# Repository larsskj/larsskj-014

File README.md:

A board hosting pogo pins
=========================

### larsskj-014

This project is a board hosting a couple of pogo pins intended to supply power to structures and other scale models.

The board has a diameter of 29 mm intended to be mounted in a 30 mm hole. The distance between the pogo pins is 10 mm.

For more information, visit the [project homepage](https://larsskj.org/projects/larsskj-014).

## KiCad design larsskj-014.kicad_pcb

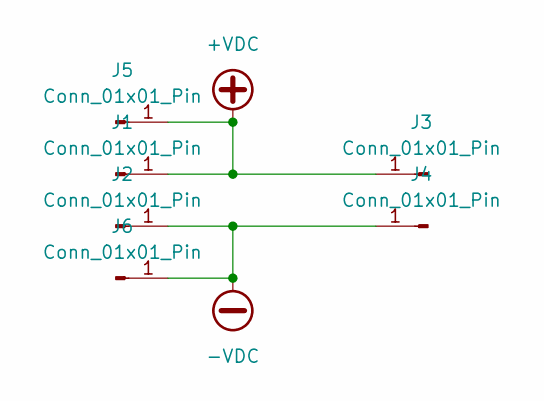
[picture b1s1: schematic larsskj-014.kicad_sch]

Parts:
J1, J2, J5, J6: Conn_01x01_Pin; MountingHole_2.2mm_M2_Pad_Via
J3, J4: Conn_01x01_Pin; Pogo_Pin_YZ227415084P-01; LCSC C5157269

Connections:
+VDC: J1.1, J3.1, J5.1
-VDC: J2.1, J4.1, J6.1

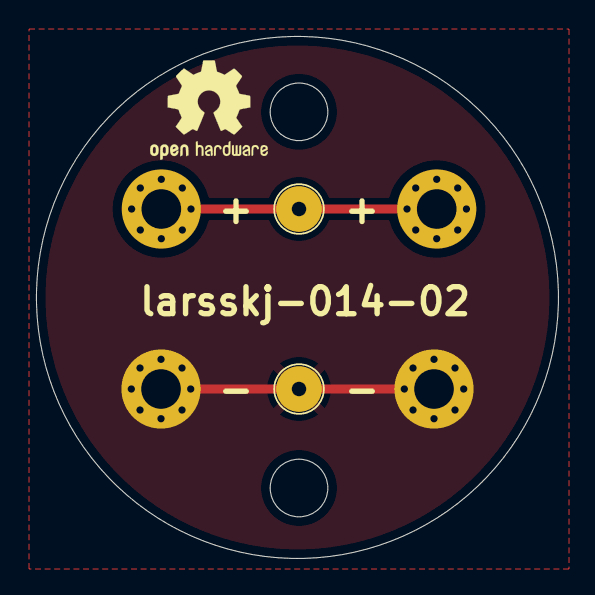
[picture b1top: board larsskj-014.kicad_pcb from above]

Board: 2 copper layers, 29.0 x 29.0 mm, 6 parts (0 on the bottom side), 2 nets.

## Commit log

2025-10-06 Add README.md
2025-10-17 Update metadata.
2025-10-17 Adjust to correct size.
2025-10-17 Image resize
2025-10-17 Update image
2025-10-17 Image update.
2025-10-17 Widen tracks
2025-10-18 Add local 3D models.
2025-10-26 Ready for revision #2
